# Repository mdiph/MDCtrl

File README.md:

# MDCtrl
DIY simple and ultraportable controller powered by [GP2040-CE Firmware](https://github.com/OpenStickCommunity/GP2040-CE)

---

# BOM

The component that you need to build MDCtrl:
- MDCtrl [PCB](/Ver1/pcb/)
- MDCtrl Case [(2D)](/Case/)
- Raspberry Pi Pico 
- **12** Kailh hotswap sockets (Optional)
- **12** Keyboard switches
- **12** Keycaps
- **1** Stabilizer
- **5** 6x6x5 [Tactile Switches](https://www.hdk.co.jp/pdf/eng/e291702.pdf)
- Soldering component
- Rubber Feet (For the bottom of the case)

PCB thickness should be 1,6mm (Double layer) with masking color of your choice

# Board

Board Version |   [Ver1](/Ver1/)  |  [Ver2 (WIP)](/Ver2/)  |
--------------|:-----------------:|:----------------:|
PCB Dimension | 175,418x87,312mm  | WIP              |
Board Used    | [Raspberry Pi Pico](https://www.raspberrypi.com/products/raspberry-pi-pico/) | [Waveshare RP2040-Zero](https://www.waveshare.com/rp2040-zero.htm)|
Port          | Micro USB         | USB-C            |

# Sources

PCB Design built with the following sources:
- [Firmware GP2040-CE](https://github.com/OpenStickCommunity/GP2040-CE)
- [Raspberry Pi Pico Footprint by Nicolò Carandini](https://github.com/ncarandini/KiCad-RP-Pico)
- [Keyboard Switches Footprint](https://github.com/ebastler/marbastlib)

---

Shield: [![CC BY-SA 4.0][cc-by-sa-shield]][cc-by-sa]

This work is licensed under a
[Creative Commons Attribution-ShareAlike 4.0 International License][cc-by-sa].

[![CC BY-SA 4.0][cc-by-sa-image]][cc-by-sa]

[cc-by-sa]: http://creativecommons.org/licenses/by-sa/4.0/
[cc-by-sa-image]: https://licensebuttons.net/l/by-sa/4.0/88x31.png
[cc-by-sa-shield]: https://img.shields.io/badge/License-CC%20BY--SA%204.0-lightgrey.svg

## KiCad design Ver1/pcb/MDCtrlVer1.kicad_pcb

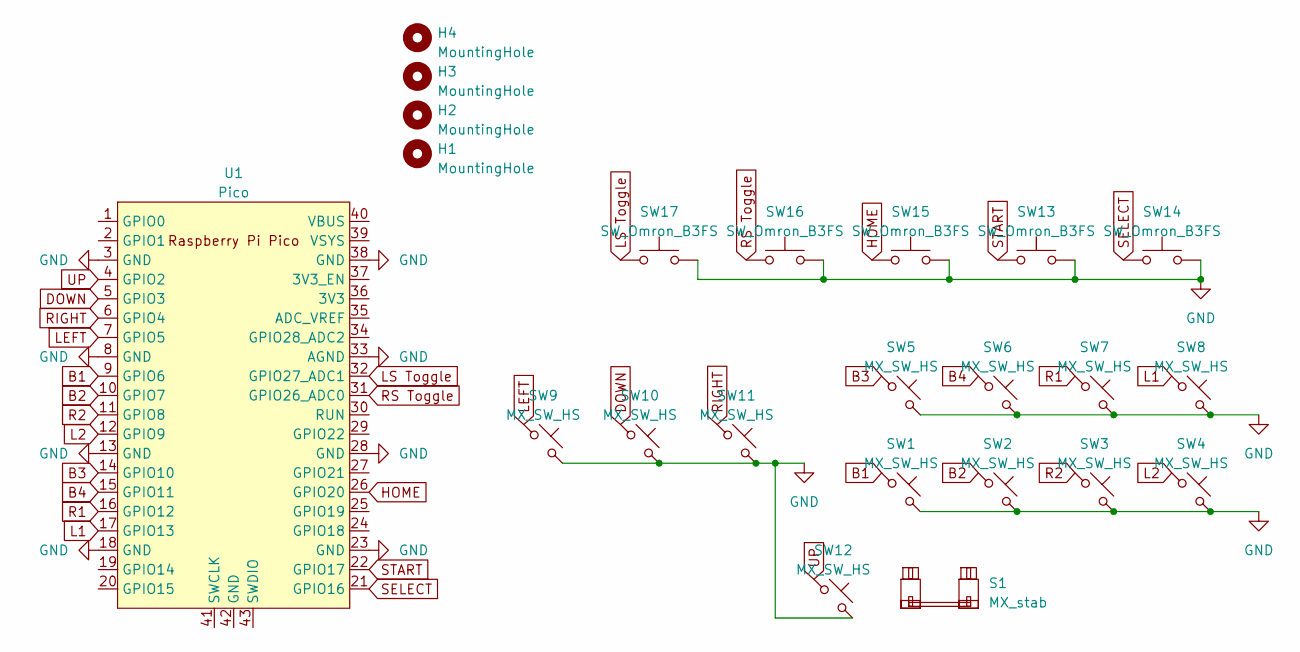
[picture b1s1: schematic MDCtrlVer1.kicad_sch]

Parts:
H1, H2, H3, H4: MountingHole; MountingHole_3.5mm
S1: MX_stab; STAB_MX_2u
SW1, SW2, SW3, SW4, SW5, SW6, SW7, SW8, SW9, SW10, SW11, SW12: MX_SW_HS; SW_MX_HS_1u
SW13, SW14, SW15, SW16, SW17: SW_Omron_B3FS; SW_PUSH_6mm_H5mm
U1: Pico; RPi_Pico_SMD_TH

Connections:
B1: SW1.1, U1.9 (GPIO6)
B2: SW2.1, U1.10 (GPIO7)
B3: SW5.1, U1.14 (GPIO10)
B4: SW6.1, U1.15 (GPIO11)
DOWN: SW10.1, U1.5 (GPIO3)
GND: SW1.2, SW2.2, SW3.2, SW4.2, SW5.2, SW6.2, SW7.2, SW8.2, SW9.2, SW10.2, SW11.2, SW12.2, SW13.2, SW14.2, SW15.2, SW16.2, SW17.2, U1.3 (GND), U1.8 (GND), U1.13 (GND), U1.18 (GND), U1.23 (GND), U1.28 (GND), U1.33 (AGND), U1.38 (GND)
HOME: SW15.1, U1.26 (GPIO20)
L1: SW8.1, U1.17 (GPIO13)
L2: SW4.1, U1.12 (GPIO9)
LEFT: SW9.1, U1.7 (GPIO5)
LS Toggle: SW17.1, U1.32 (GPIO27_ADC1)
R1: SW7.1, U1.16 (GPIO12)
R2: SW3.1, U1.11 (GPIO8)
RIGHT: SW11.1, U1.6 (GPIO4)
RS Toggle: SW16.1, U1.31 (GPIO26_ADC0)
SELECT: SW14.1, U1.21 (GPIO16)
START: SW13.1, U1.22 (GPIO17)
UP: SW12.1, U1.4 (GPIO2)

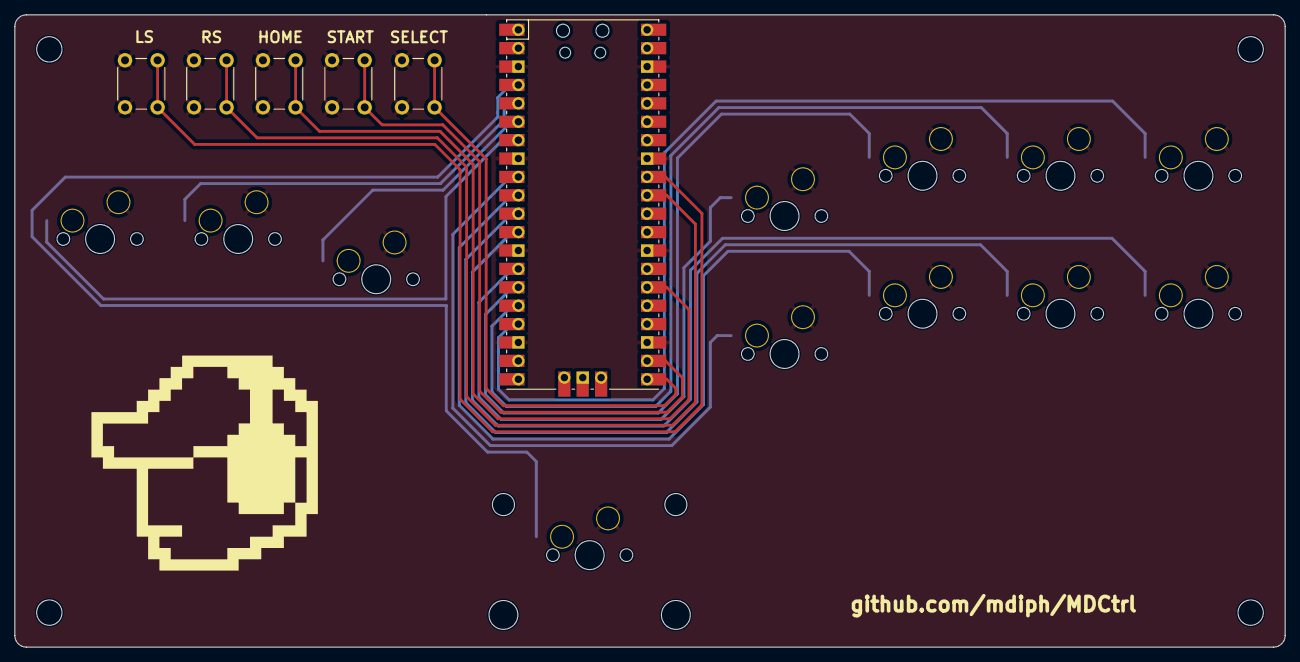
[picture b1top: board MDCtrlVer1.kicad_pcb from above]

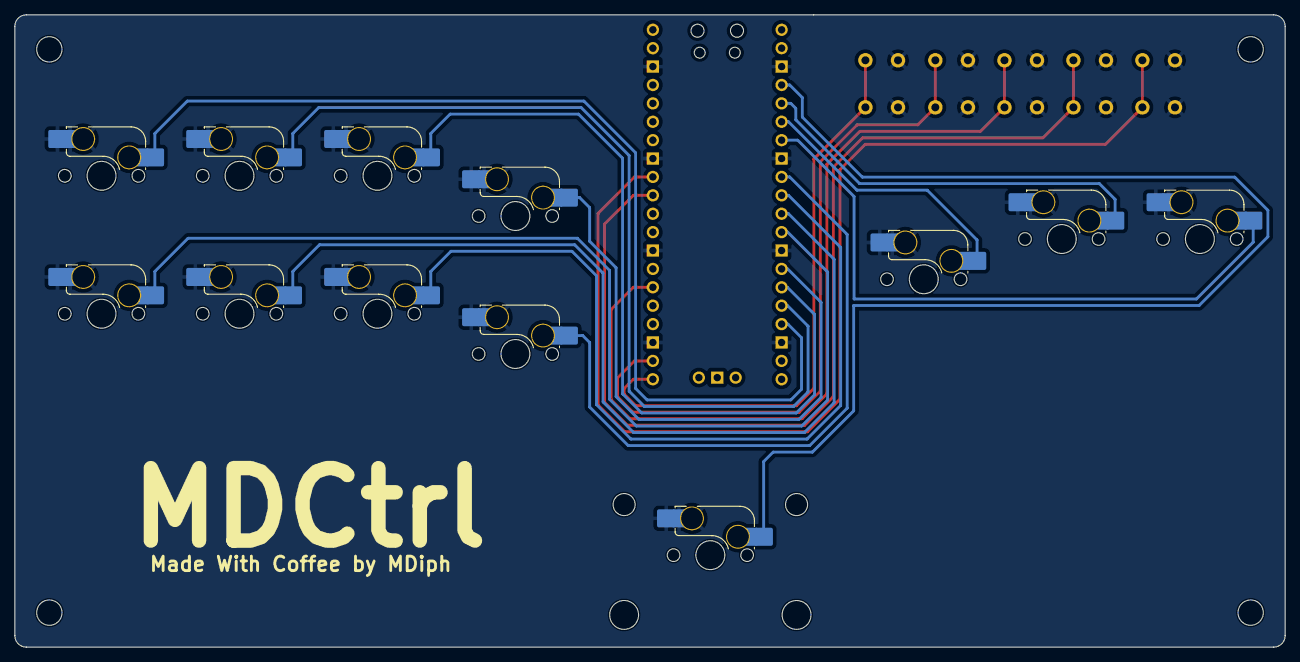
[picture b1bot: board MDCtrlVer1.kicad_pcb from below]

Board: 2 copper layers, 175.4 x 87.3 mm, 23 parts (12 on the bottom side), 18 nets.

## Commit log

2023-03-07 Added license CC-BY-SA
2023-03-07 Add CC-BY-SA License
2023-04-01 adding version 1
2023-04-01 Added pcb
2023-05-27 Updated Case
2023-05-27 Fixing stuff
2023-05-27 Fixing README
2023-05-27 Fixing link
2023-05-28 adding minor changes
2023-05-28 adding table
2023-05-30 Fixing dxf files
